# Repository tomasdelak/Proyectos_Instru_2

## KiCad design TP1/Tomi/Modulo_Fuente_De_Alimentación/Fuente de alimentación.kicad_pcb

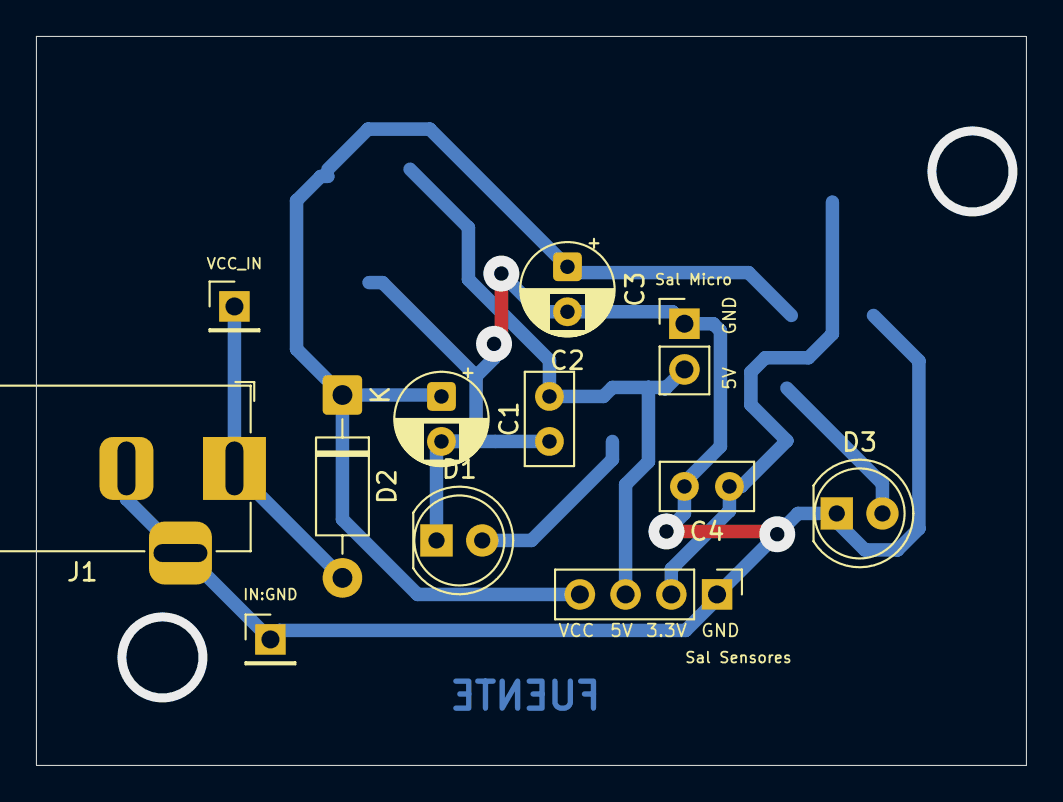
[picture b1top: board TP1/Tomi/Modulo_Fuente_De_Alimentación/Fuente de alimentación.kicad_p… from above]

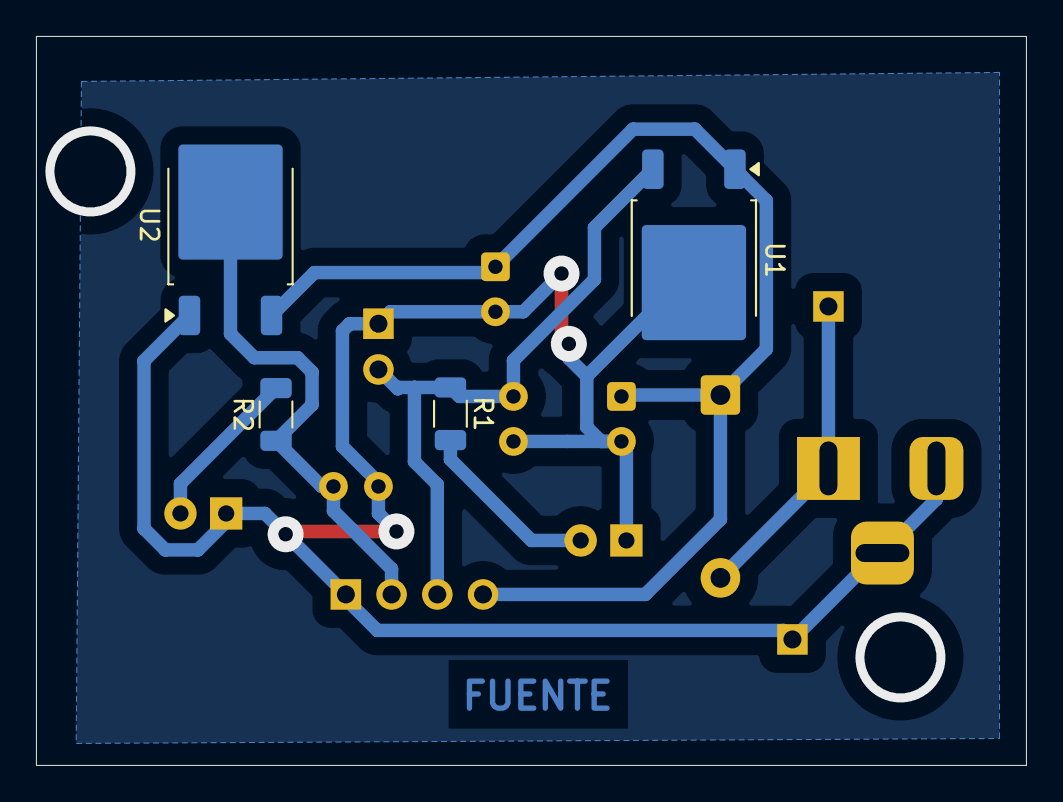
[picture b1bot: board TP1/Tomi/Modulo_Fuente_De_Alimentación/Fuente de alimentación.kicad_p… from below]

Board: 2 copper layers, 55.0 x 40.5 mm, 16 parts (4 on the bottom side), 7 nets.

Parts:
C1: 10 uf x 16V; CP_Radial_D5.0mm_P2.50mm
C2: 22pf; C_Disc_D5.0mm_W2.5mm_P2.50mm
C3: 10 uFx16V; CP_Radial_D5.0mm_P2.50mm
C4: 20pF; C_Disc_D5.0mm_W2.5mm_P2.50mm
D1, D3: 5V; LED_D5.0mm
D2: 1N4007; D_DO-41_SOD81_P10.16mm_Horizontal
IN:GND: Conn_01x01_Pin; PinHeader_1x01_P2.54mm_Vertical
J1: Barrel_Jack_Switch; BarrelJack_Horizontal
R1, R2: 1k; R_1206_3216Metric
Sal Micro: Conn_01x02_Pin; PinHeader_1x02_P2.54mm_Vertical
Sal Sensores: Conn_01x04_Pin; PinHeader_1x04_P2.54mm_Vertical
U1: L7805; TO-252-2
U2: AZ1117-3.3; TO-252-2
VCC_IN: Conn_01x01_Pin; PinHeader_1x01_P2.54mm_Vertical

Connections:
/3.3V: C4.1, R2.1, Sal Sensores.2, U2.2 (VO)
/5V: C2.1, R1.1, Sal Micro.2, Sal Sensores.3, U1.3 (OUT)
/GND: C1.2, C2.2, C3.2, C4.2, D1.1 (K), D3.1 (K), IN:GND.1, J1.2, J1.3, Sal Micro.1, Sal Sensores.1, U1.2 (GND), U2.1 (GND)
/VCC: C1.1, C3.1, D2.1 (K), Sal Sensores.4, U1.1 (IN), U2.3 (VI)
/VCC_IN: D2.2 (A), J1.1, VCC_IN.1
unnamed: D1.2 (A), R1.2
unnamed: D3.2 (A), R2.2

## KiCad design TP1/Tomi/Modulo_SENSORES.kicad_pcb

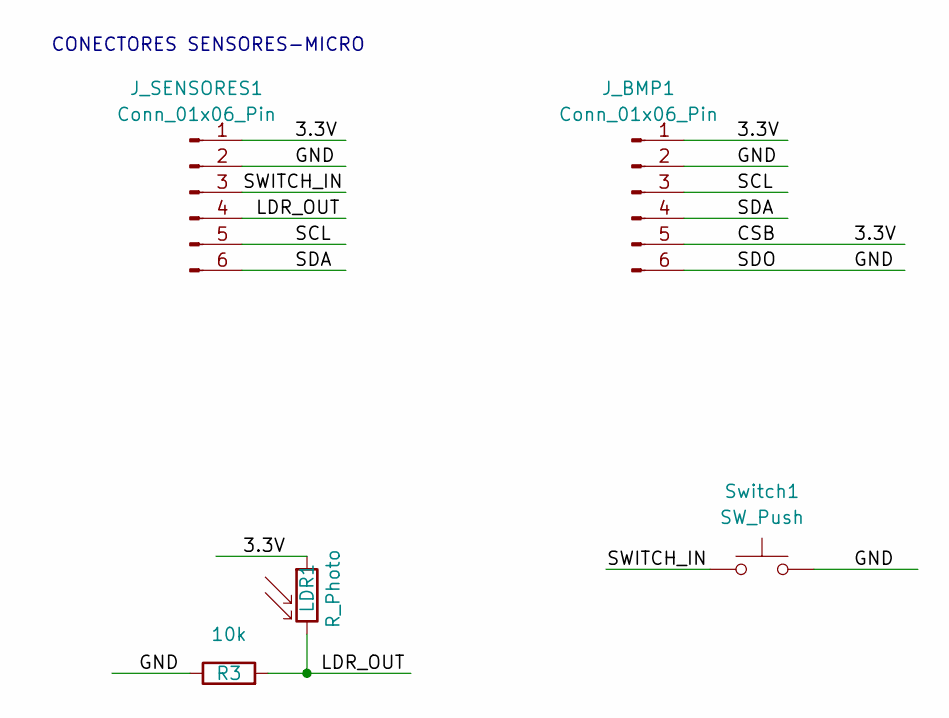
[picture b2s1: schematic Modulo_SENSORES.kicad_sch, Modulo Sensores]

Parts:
J_BMP1: Conn_01x06_Pin; PinHeader_1x06_P2.54mm_Vertical
J_SENSORES1: Conn_01x06_Pin; PinHeader_1x06_P2.54mm_Vertical
LDR1: R_Photo; R_LDR_4.9x4.2mm_P2.54mm_Vertical
R3: 10k; R_Axial_DIN0204_L3.6mm_D1.6mm_P7.62mm_Horizontal
Switch1: SW_Push; SW_PUSH_6mm

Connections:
/3.3V: J_BMP1.1, J_BMP1.5, J_SENSORES1.1, LDR1.1
/GND: J_BMP1.2, J_BMP1.6, J_SENSORES1.2, R3.1, Switch1.2
/LDR_OUT: J_SENSORES1.4, LDR1.2, R3.2
/SCL: J_BMP1.3, J_SENSORES1.5
/SDA: J_BMP1.4, J_SENSORES1.6
/SWITCH_IN: J_SENSORES1.3, Switch1.1

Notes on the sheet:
CONECTORES SENSORES-MICRO

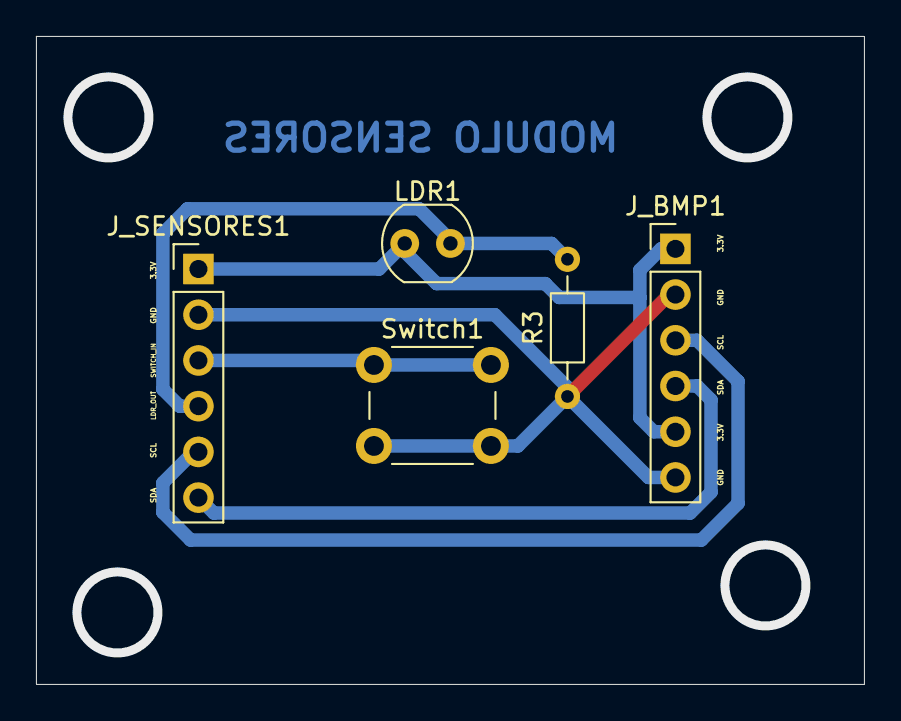
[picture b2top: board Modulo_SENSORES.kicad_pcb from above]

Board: 2 copper layers, 46.0 x 36.0 mm, 5 parts (0 on the bottom side), 6 nets.

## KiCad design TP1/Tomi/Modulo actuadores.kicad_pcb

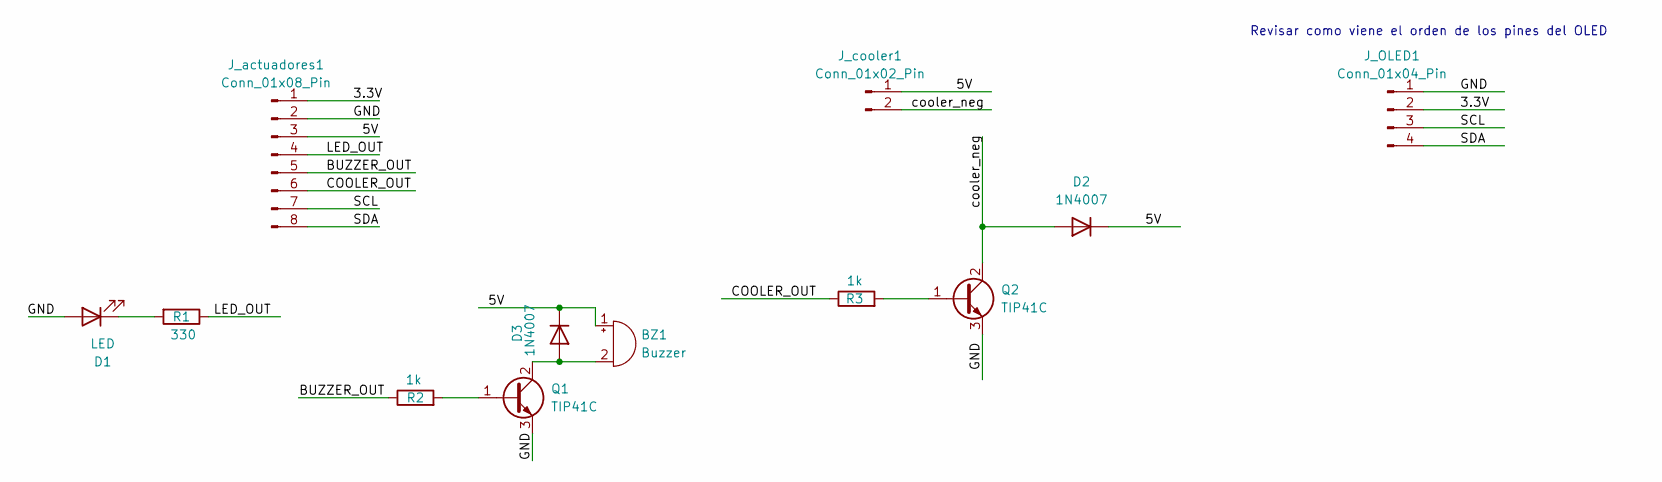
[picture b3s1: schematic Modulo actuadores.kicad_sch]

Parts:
BZ1: Buzzer; Buzzer_12x9.5RM7.6
D1: LED; LED_D5.0mm
D2, D3: 1N4007; D_DO-41_SOD81_P10.16mm_Horizontal
J_OLED1: Conn_01x04_Pin; PinHeader_1x04_P2.54mm_Vertical
J_actuadores1: Conn_01x08_Pin; PinHeader_1x08_P2.54mm_Vertical
J_cooler1: Conn_01x02_Pin; PinHeader_1x02_P2.54mm_Vertical
Q1, Q2: TIP41C; TO-220-3_Vertical
R1: 330; R_Axial_DIN0204_L3.6mm_D1.6mm_P7.62mm_Horizontal
R2, R3: 1k; R_Axial_DIN0204_L3.6mm_D1.6mm_P7.62mm_Horizontal

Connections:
/3.3V: J_OLED1.2, J_actuadores1.1; also elsewhere on the board
/5V: BZ1.1 (+), D2.1 (K), D3.1 (K), J_actuadores1.3, J_cooler1.1; also elsewhere on the board
/BUZZER_OUT: J_actuadores1.5, R2.1; also elsewhere on the board
/COOLER_OUT: J_actuadores1.6, R3.1; also elsewhere on the board
/GND: D1.2 (A), J_OLED1.1, J_actuadores1.2, Q1.3 (E), Q2.3 (E); also elsewhere on the board
/LED_OUT: J_actuadores1.4, R1.1; also elsewhere on the board
/SCL: J_OLED1.3, J_actuadores1.7; also elsewhere on the board
/SDA: J_OLED1.4, J_actuadores1.8; also elsewhere on the board
/cooler_neg: D2.2 (A), J_cooler1.2, Q2.2 (C)
unnamed: BZ1.2 (-), D3.2 (A), Q1.2 (C)
unnamed: D1.1 (K), R1.2
unnamed: Q1.1 (B), R2.2
unnamed: Q2.1 (B), R3.2

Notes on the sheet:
Revisar como viene el orden de los pines del OLED

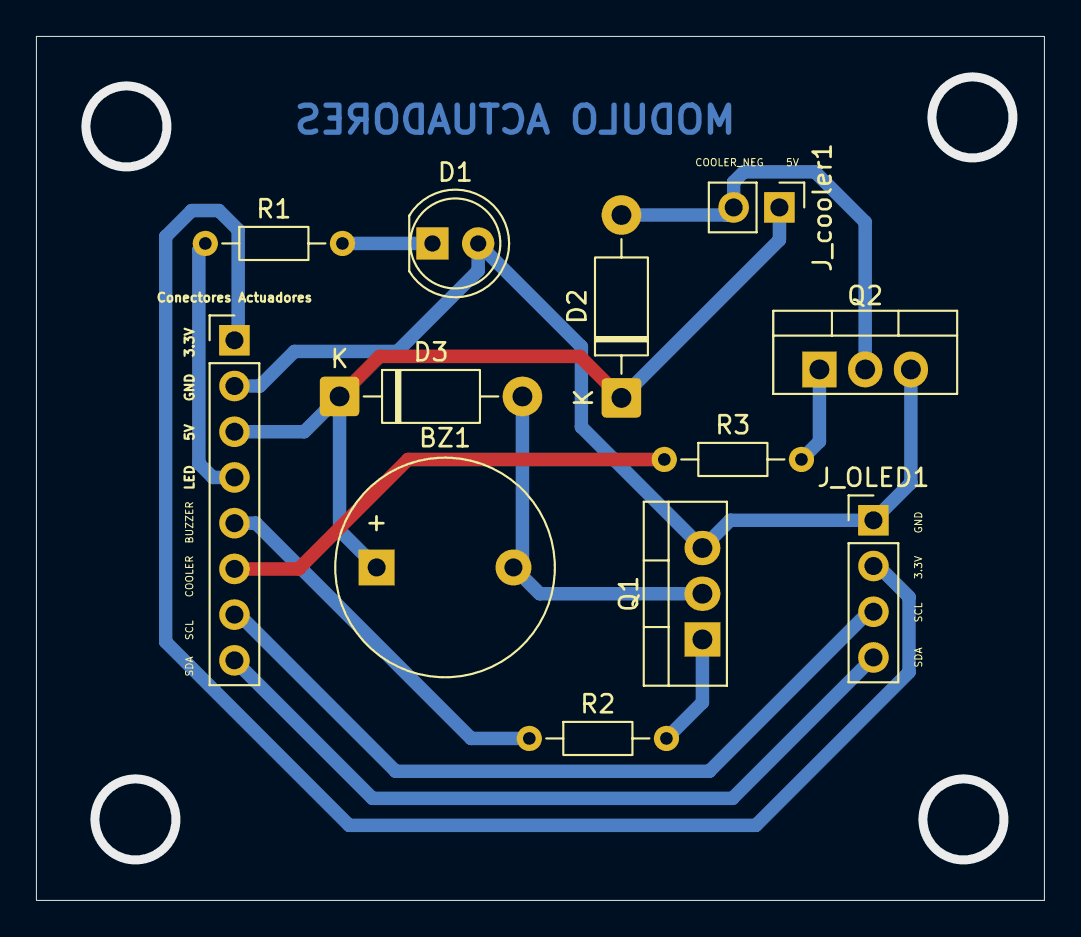
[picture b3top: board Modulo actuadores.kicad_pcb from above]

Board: 2 copper layers, 56.0 x 48.0 mm, 12 parts (0 on the bottom side), 13 nets.

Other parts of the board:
Conectores Actuadores: Conn_01x08_Pin; PinHeader_1x08_P2.54mm_Vertical

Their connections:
/3.3V: Conectores Actuadores.1; also elsewhere on the board
/5V: Conectores Actuadores.3; also elsewhere on the board
/BUZZER_OUT: Conectores Actuadores.5; also elsewhere on the board
/COOLER_OUT: Conectores Actuadores.6; also elsewhere on the board
/GND: Conectores Actuadores.2; also elsewhere on the board
/LED_OUT: Conectores Actuadores.4; also elsewhere on the board
/SCL: Conectores Actuadores.7; also elsewhere on the board
/SDA: Conectores Actuadores.8; also elsewhere on the board

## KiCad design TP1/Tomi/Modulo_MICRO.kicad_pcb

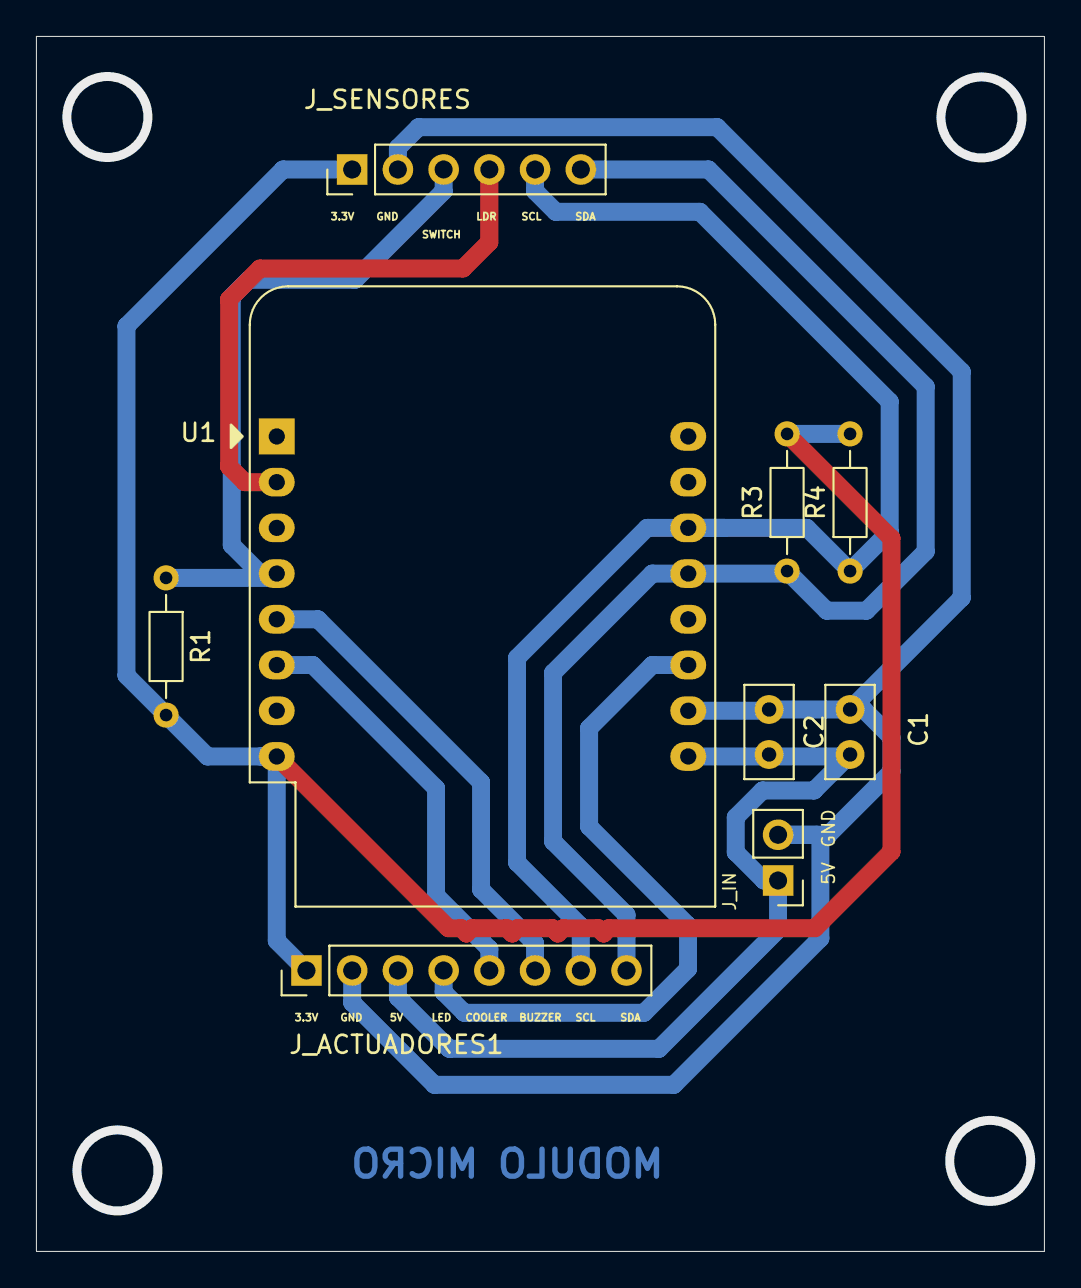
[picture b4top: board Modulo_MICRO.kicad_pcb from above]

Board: 2 copper layers, 56.0 x 67.5 mm, 9 parts (0 on the bottom side), 10 nets.

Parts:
C1: 100 nf x 5V; C_Disc_D5.0mm_W2.5mm_P2.50mm
C2: 10 uf x 5V; C_Disc_D5.0mm_W2.5mm_P2.50mm
J_ACTUADORES1: Conn_01x08_Pin; PinHeader_1x08_P2.54mm_Vertical
J_IN: Conn_01x02_Pin; PinHeader_1x02_P2.54mm_Vertical
J_SENSORES: Conn_01x06_Pin; PinHeader_1x06_P2.54mm_Vertical
R1: 10 k; R_Axial_DIN0204_L3.6mm_D1.6mm_P7.62mm_Horizontal
R3, R4: 4.7K; R_Axial_DIN0204_L3.6mm_D1.6mm_P7.62mm_Horizontal
U1: WEMOS_D1_mini; WEMOS_D1_mini_light

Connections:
/3.3V: J_ACTUADORES1.1, J_SENSORES.1, R1.2, R3.2, R4.2, U1.8 (3V3)
/5V: C1.2, C2.2, J_ACTUADORES1.3, J_IN.1, U1.9 (5V)
/BUZZER_OUT: J_ACTUADORES1.6, U1.5 (MISO/D6)
/COOLER_OUT: J_ACTUADORES1.5, U1.6 (MOSI/D7)
/GND: C1.1, C2.1, J_ACTUADORES1.2, J_IN.2, J_SENSORES.2, U1.10 (GND)
/LDR_OUT: J_SENSORES.4, U1.2 (A0)
/LED_OUT: J_ACTUADORES1.4, U1.11 (D4)
/SCL: J_ACTUADORES1.7, J_SENSORES.5, R4.1, U1.14 (SCL/D1)
/SDA: J_ACTUADORES1.8, J_SENSORES.6, R3.1, U1.13 (SDA/D2)
/SWITCH_IN: J_SENSORES.3, R1.1, U1.4 (SCK/D5)

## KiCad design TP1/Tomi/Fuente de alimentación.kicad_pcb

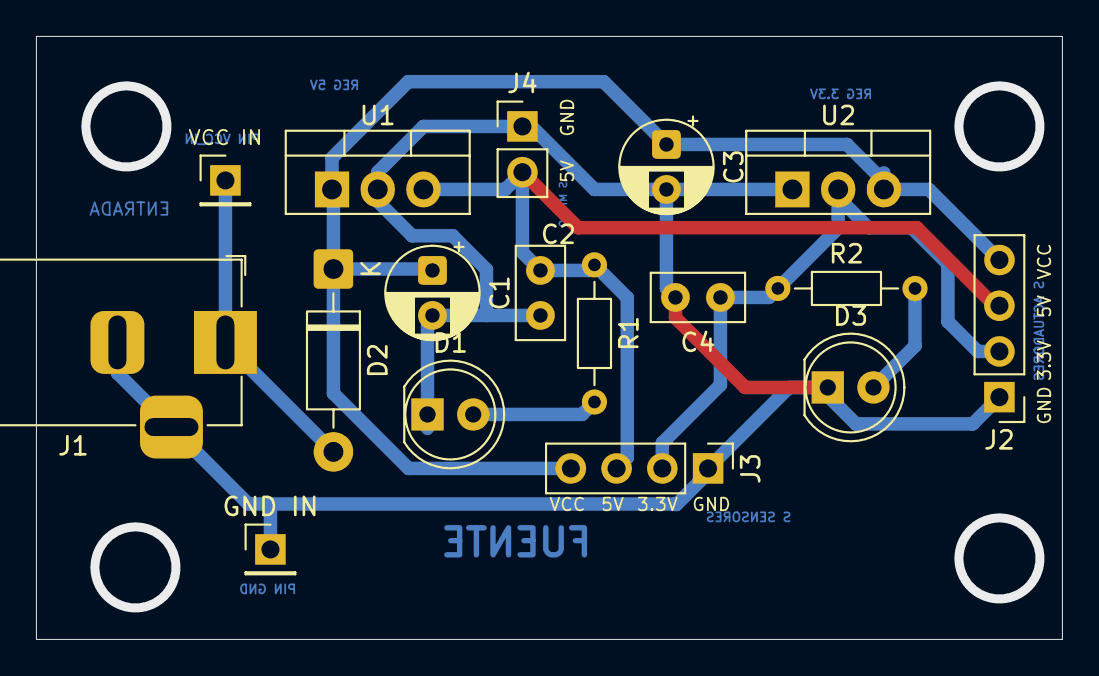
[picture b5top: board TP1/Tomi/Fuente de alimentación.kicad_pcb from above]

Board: 2 copper layers, 57.0 x 33.5 mm, 17 parts (0 on the bottom side), 7 nets.

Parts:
C1: 10 uf x 16V; CP_Radial_D5.0mm_P2.50mm
C2: 22pf; C_Disc_D5.0mm_W2.5mm_P2.50mm
C3: 10 uFx16V; CP_Radial_D5.0mm_P2.50mm
C4: 20pF; C_Disc_D5.0mm_W2.5mm_P2.50mm
D1, D3: 5V; LED_D5.0mm
D2: 1N4007; D_DO-41_SOD81_P10.16mm_Horizontal
GND IN: Conn_01x01_Pin; PinHeader_1x01_P2.54mm_Vertical
J1: Barrel_Jack_Switch; BarrelJack_Horizontal
J2, J3: Conn_01x04_Pin; PinHeader_1x04_P2.54mm_Vertical
J4: Conn_01x02_Pin; PinHeader_1x02_P2.54mm_Vertical
R1, R2: 1k; R_Axial_DIN0204_L3.6mm_D1.6mm_P7.62mm_Horizontal
U1: L7805; TO-220-3_Vertical
U2: AZ1117-3.3; TO-220-3_Vertical
VCC IN: Conn_01x01_Pin; PinHeader_1x01_P2.54mm_Vertical

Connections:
/3.3V: C4.1, J2.2, J3.2, R2.1, U2.2 (VO)
/5V: C2.1, J2.3, J3.3, J4.2, R1.1, U1.3 (OUT)
/GND: C1.2, C2.2, C3.2, C4.2, D1.1 (K), D3.1 (K), GND IN.1, J1.2, J1.3, J2.1, J3.1, J4.1, U1.2 (GND), U2.1 (GND)
/VCC: C1.1, C3.1, D2.1 (K), J2.4, J3.4, U1.1 (IN), U2.3 (VI)
/VCC_IN: D2.2 (A), J1.1, VCC IN.1
unnamed: D1.2 (A), R1.2
unnamed: D3.2 (A), R2.2

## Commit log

2026-03-07 Create TP1
2026-03-07 Create .gitkeep Carpeta tomi
2026-03-08 actualizo pcb
2026-03-08 modulo micro
2026-03-10 Modulo actuadores Versión tomi
2026-03-12 Modulo sensores
2026-03-12 Create .gitkeep carpeta modulo micro
2026-03-12 Create .gitkeep carpeta modulo fuente de alimentación
2026-03-12 Create .gitkeep Modulo Actuadores
2026-03-12 Create .gitkeep Módulo sensores
2026-03-13 Fuente con SMD
